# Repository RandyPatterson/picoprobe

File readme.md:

# Pico Probe 
Using the Raspberry Pi Pico as a SWD (Software Debug) Probe.  Simple schematic and PCB to easily setup a Raspberry Pi PICO and a Pico Probe

## platformio.ini settings 
```ini
[env:pico]
platform = raspberrypi
board = pico
framework = arduino
debug_tool = picoprobe
upload_protocol = picoprobe
;start debugging at sketch setup() otherwise start in RTOS main
debug_init_break = tbreak setup

```
Be sure to use zadig to replace the USB driver on **Picoprobe (Interface 2)** to **libusb-win32** (Windows)

Device Manager

### Connection Diagram

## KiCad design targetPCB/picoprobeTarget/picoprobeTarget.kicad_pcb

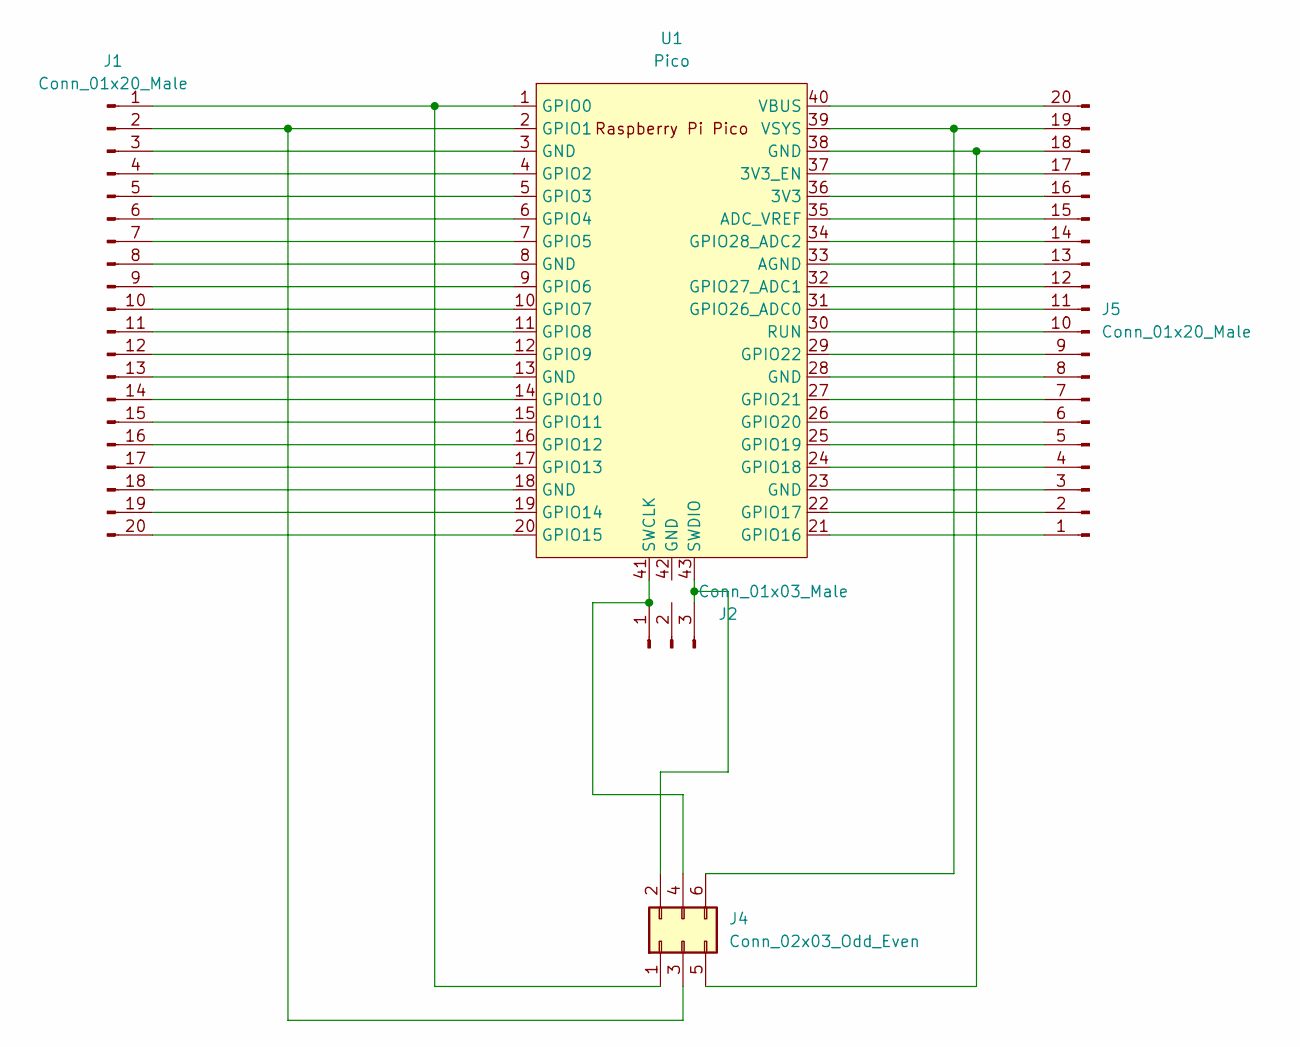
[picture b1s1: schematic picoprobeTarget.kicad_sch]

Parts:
J1, J5: Conn_01x20_Male; PinSocket_1x20_P2.54mm_Vertical
J2: Conn_01x03_Male; PinSocket_1x03_P2.54mm_Vertical
J4: Conn_02x03_Odd_Even; IDC-Header_2x03_P2.54mm_Vertical
U1: Pico; RPi_Pico_SMD_TH

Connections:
unnamed: J1.1, J4.1, U1.1 (GPIO0)
unnamed: J1.2, J4.3, U1.2 (GPIO1)
unnamed: J1.3, U1.3 (GND)
unnamed: J1.4, U1.4 (GPIO2)
unnamed: J1.5, U1.5 (GPIO3)
unnamed: J1.6, U1.6 (GPIO4)
unnamed: J1.7, U1.7 (GPIO5)
unnamed: J1.8, U1.8 (GND)
unnamed: J1.9, U1.9 (GPIO6)
unnamed: J1.10, U1.10 (GPIO7)
unnamed: J1.11, U1.11 (GPIO8)
unnamed: J1.12, U1.12 (GPIO9)
unnamed: J1.13, U1.13 (GND)
unnamed: J1.14, U1.14 (GPIO10)
unnamed: J1.15, U1.15 (GPIO11)
unnamed: J1.16, U1.16 (GPIO12)
unnamed: J1.17, U1.17 (GPIO13)
unnamed: J1.18, U1.18 (GND)
unnamed: J1.19, U1.19 (GPIO14)
unnamed: J1.20, U1.20 (GPIO15)
unnamed: J2.1, J4.4, U1.41 (SWCLK)
unnamed: J2.3, J4.2, U1.43 (SWDIO)
unnamed: J4.5, J5.18, U1.38 (GND)
unnamed: J4.6, J5.19, U1.39 (VSYS)
unnamed: J5.1, U1.21 (GPIO16)
unnamed: J5.2, U1.22 (GPIO17)
unnamed: J5.3, U1.23 (GND)
unnamed: J5.4, U1.24 (GPIO18)
unnamed: J5.5, U1.25 (GPIO19)
unnamed: J5.6, U1.26 (GPIO20)
unnamed: J5.7, U1.27 (GPIO21)
unnamed: J5.8, U1.28 (GND)
unnamed: J5.9, U1.29 (GPIO22)
unnamed: J5.10, U1.30 (RUN)
unnamed: J5.11, U1.31 (GPIO26_ADC0)
unnamed: J5.12, U1.32 (GPIO27_ADC1)
unnamed: J5.13, U1.33 (AGND)
unnamed: J5.14, U1.34 (GPIO28_ADC2)
unnamed: J5.15, U1.35 (ADC_VREF)
unnamed: J5.16, U1.36 (3V3)
unnamed: J5.17, U1.37 (3V3_EN)
unnamed: J5.20, U1.40 (VBUS)

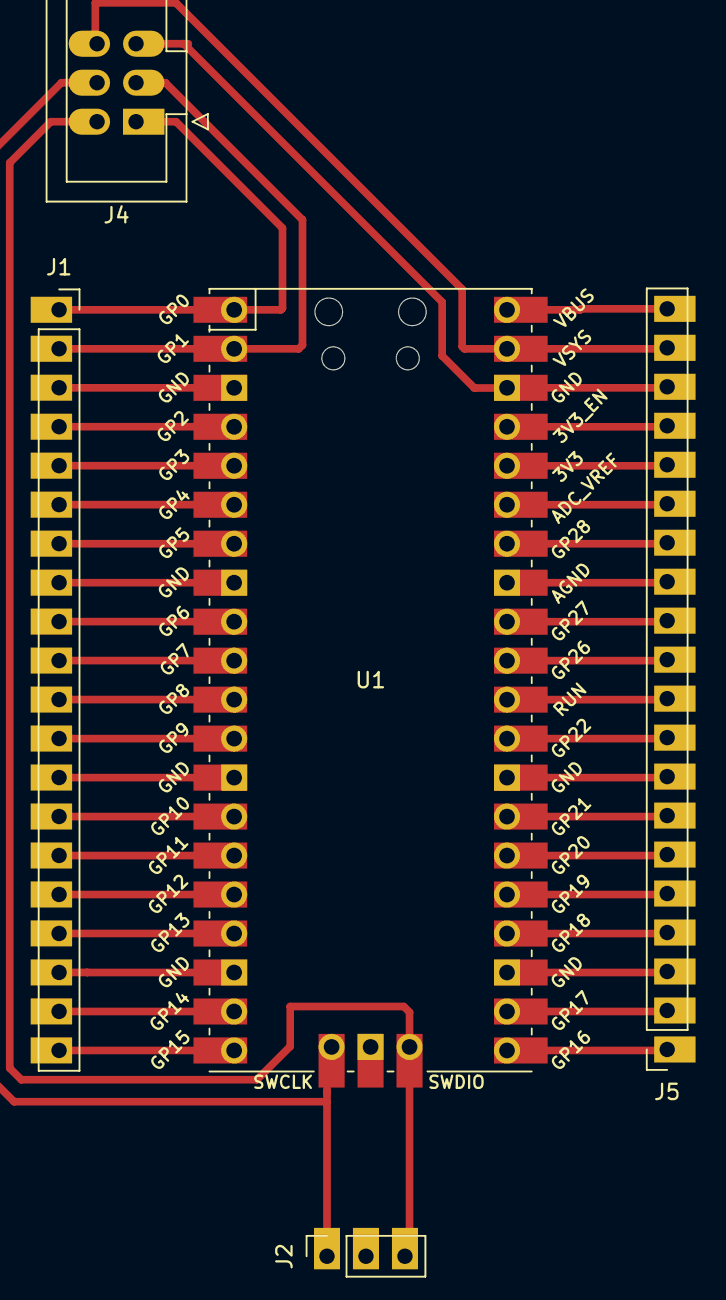
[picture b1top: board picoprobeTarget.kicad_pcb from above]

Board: 2 copper layers, 5 parts (0 on the bottom side), 42 nets.

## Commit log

2022-07-20 Schematic & PCB v1
2022-07-20 update readme image links
2022-07-21 add wiring diagram
2023-08-07 Updated to release board with picoprobe support
2023-08-07 minor updates to readme
